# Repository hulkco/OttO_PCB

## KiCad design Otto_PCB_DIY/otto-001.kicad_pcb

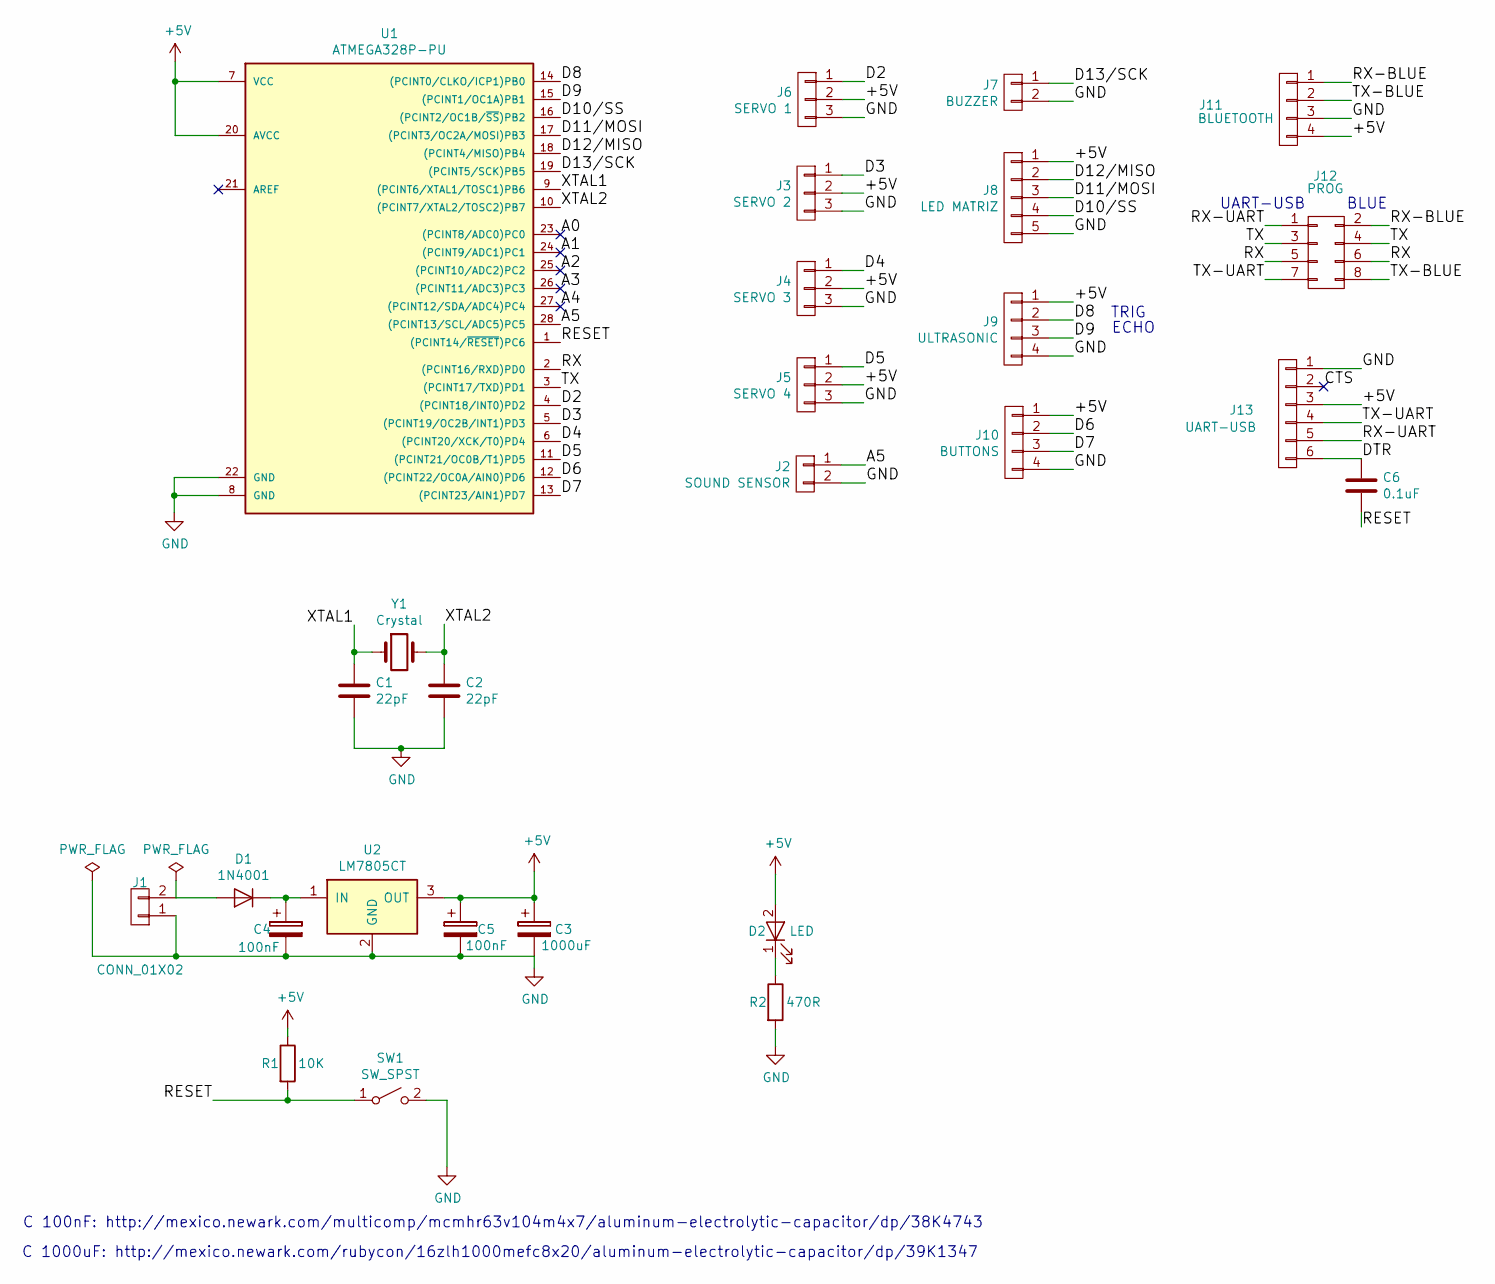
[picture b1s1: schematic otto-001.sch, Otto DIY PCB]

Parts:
C1, C2: 22pF; C_Disc_D5.0mm_W2.5mm_P2.50mm
C3: 1000uF; CP_Radial_D8.0mm_P3.50mm
C4, C5: 100nF; CP_Radial_D4.0mm_P1.50mm
C6: 0.1uF; C_Disc_D5.0mm_W2.5mm_P2.50mm
D1: 1N4001; DIODE-DO-41
D2: LED; LED_D3.0mm
J1: CONN_01X02; Pin_Header_Straight_1x02_Pitch2.54mm
J2: SOUND SENSOR; Pin_Header_Straight_1x02_Pitch2.54mm
J3: SERVO 2; Pin_Header_Straight_1x03_Pitch2.54mm
J4: SERVO 3; Pin_Header_Straight_1x03_Pitch2.54mm
J5: SERVO 4; Pin_Header_Straight_1x03_Pitch2.54mm
J6: SERVO 1; Pin_Header_Straight_1x03_Pitch2.54mm
J7: BUZZER; Pin_Header_Straight_1x02_Pitch2.54mm
J8: LED MATRIZ; Pin_Header_Straight_1x05_Pitch2.54mm
J9: ULTRASONIC; Pin_Header_Straight_1x04_Pitch2.54mm
J10: BUTTONS; Pin_Header_Straight_1x04_Pitch2.54mm
J11: BLUETOOTH; Pin_Header_Straight_1x04_Pitch2.54mm
J12: PROG; Socket_Strip_Straight_2x04_Pitch2.54mm
J13: UART-USB; Pin_Header_Straight_1x06_Pitch2.54mm
R1: 10K; R_Axial_DIN0207_L6.3mm_D2.5mm_P10.16mm_Horizontal
R2: 470R; R_Axial_DIN0207_L6.3mm_D2.5mm_P10.16mm_Horizontal
SW1: SW_SPST; SW_PUSH_6mm_h4.3mm
U1: ATMEGA328P-PU; DIP-28_W7.62mm
U2: LM7805CT; TO-220_Horizontal
Y1: Crystal; Crystal_HC49-U_Vertical

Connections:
+5V: C3.1, C5.1, D2.2 (A), J3.2, J4.2, J5.2, J6.2, J8.1, J9.1, J10.1, J11.4, J13.3, R1.1, U1.7 (VCC), U1.20 (AVCC), U2.3 (OUT)
/A0: U1.23 ((PCINT8/ADC0)PC0)
/A1: U1.24 ((PCINT9/ADC1)PC1)
/A2: U1.25 ((PCINT10/ADC2)PC2)
/A3: U1.26 ((PCINT11/ADC3)PC3)
/A4: U1.27 ((PCINT12/SDA/ADC4)PC4)
/A5: J2.1, U1.28 ((PCINT13/SCL/ADC5)PC5)
/CTS: J13.2
/D2: J6.1, U1.4 ((PCINT18/INT0)PD2)
/D3: J3.1, U1.5 ((PCINT19/OC2B/INT1)PD3)
/D4: J4.1, U1.6 ((PCINT20/XCK/T0)PD4)
/D5: J5.1, U1.11 ((PCINT21/OC0B/T1)PD5)
/D6: J10.2, U1.12 ((PCINT22/OC0A/AIN0)PD6)
/D7: J10.3, U1.13 ((PCINT23/AIN1)PD7)
/D8: J9.2, U1.14 ((PCINT0/CLKO/ICP1)PB0)
/D9: J9.3, U1.15 ((PCINT1/OC1A)PB1)
/D10/SS: J8.4, U1.16 ((PCINT2/OC1B/~SS~)PB2)
/D11/MOSI: J8.3, U1.17 ((PCINT3/OC2A/MOSI)PB3)
/D12/MISO: J8.2, U1.18 ((PCINT4/MISO)PB4)
/D13/SCK: J7.1, U1.19 ((PCINT5/SCK)PB5)
/DTR: C6.1, J13.6
/RESET: C6.2, R1.2, SW1.1 (A), U1.1 ((PCINT14/~RESET~)PC6)
/RX: J12.5, J12.6, U1.2 ((PCINT16/RXD)PD0)
/RX-BLUE: J11.1, J12.2
/RX-UART: J12.1, J13.5
/TX: J12.3, J12.4, U1.3 ((PCINT17/TXD)PD1)
/TX-BLUE: J11.2, J12.8
/TX-UART: J12.7, J13.4
/XTAL1: C1.1, U1.9 ((PCINT6/XTAL1/TOSC1)PB6), Y1.1
/XTAL2: C2.1, U1.10 ((PCINT7/XTAL2/TOSC2)PB7), Y1.2
GND: C1.2, C2.2, C3.2, C4.2, C5.2, J1.1, J2.2, J3.3, J4.3, J5.3, J6.3, J7.2, J8.5, J9.4, J10.4, J11.3, J13.1, R2.2, SW1.2 (B), U1.8 (GND), U1.22 (GND), U2.2 (GND)
unnamed: C4.1, D1.1 (K), U2.1 (IN)
unnamed: D1.2 (A), J1.2
unnamed: D2.1 (K), R2.1

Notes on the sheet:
TRIG
ECHO
C 100nF: http://mexico.newark.com/multicomp/mcmhr63v104m4x7/aluminum-electrolytic-capacitor/dp/38K4743
C 1000uF: http://mexico.newark.com/rubycon/16zlh1000mefc8x20/aluminum-electrolytic-capacitor/dp/39K1347
UART-USB
BLUE

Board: 2 copper layers, 33 parts (0 on the bottom side), 28 nets, no tracks yet.

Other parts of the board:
GBSilk***: LOGO; greynaga6-2
GS***: v; greynaga6-2-cooper
HOLE1, HOLE2, HOLE3, HOLE4: MountingHole_2.2mm_M2_Pad_Via

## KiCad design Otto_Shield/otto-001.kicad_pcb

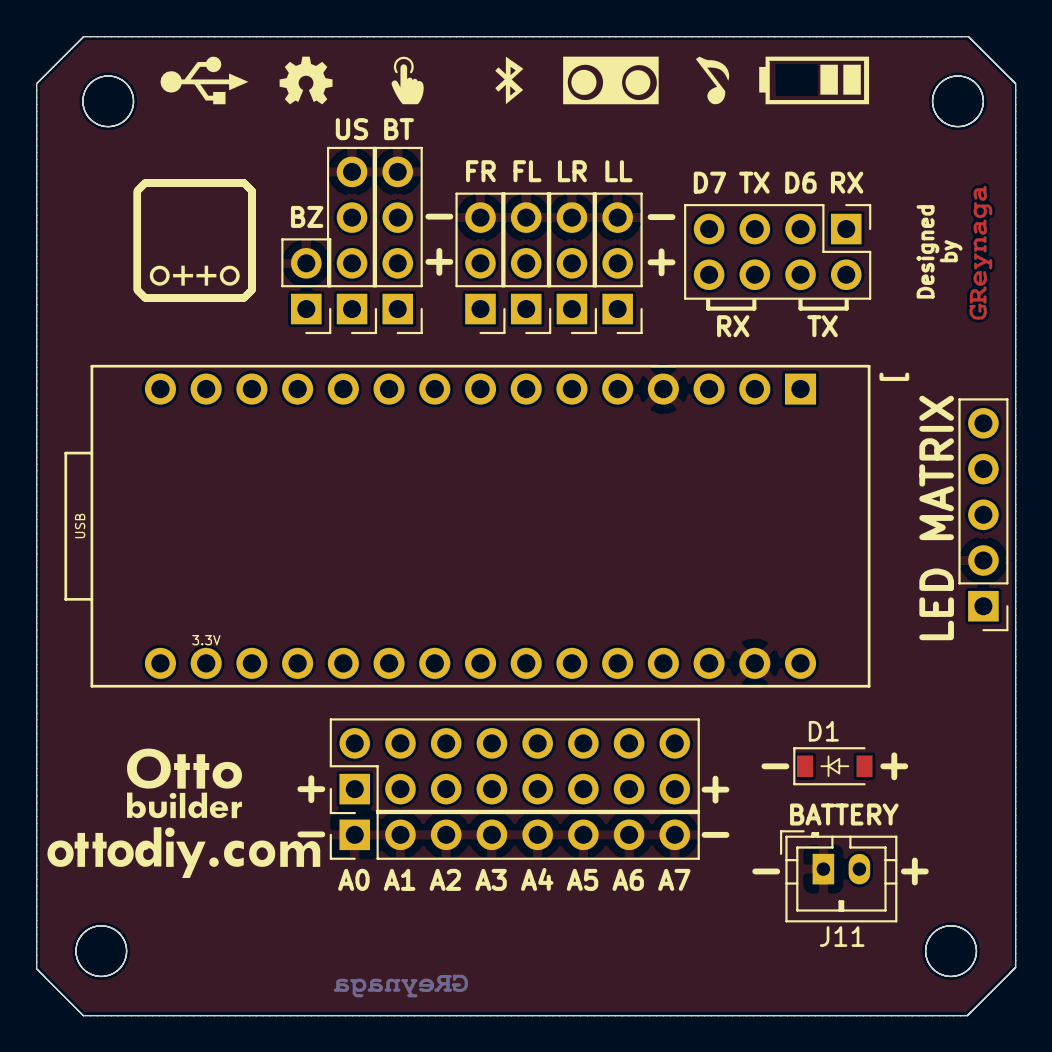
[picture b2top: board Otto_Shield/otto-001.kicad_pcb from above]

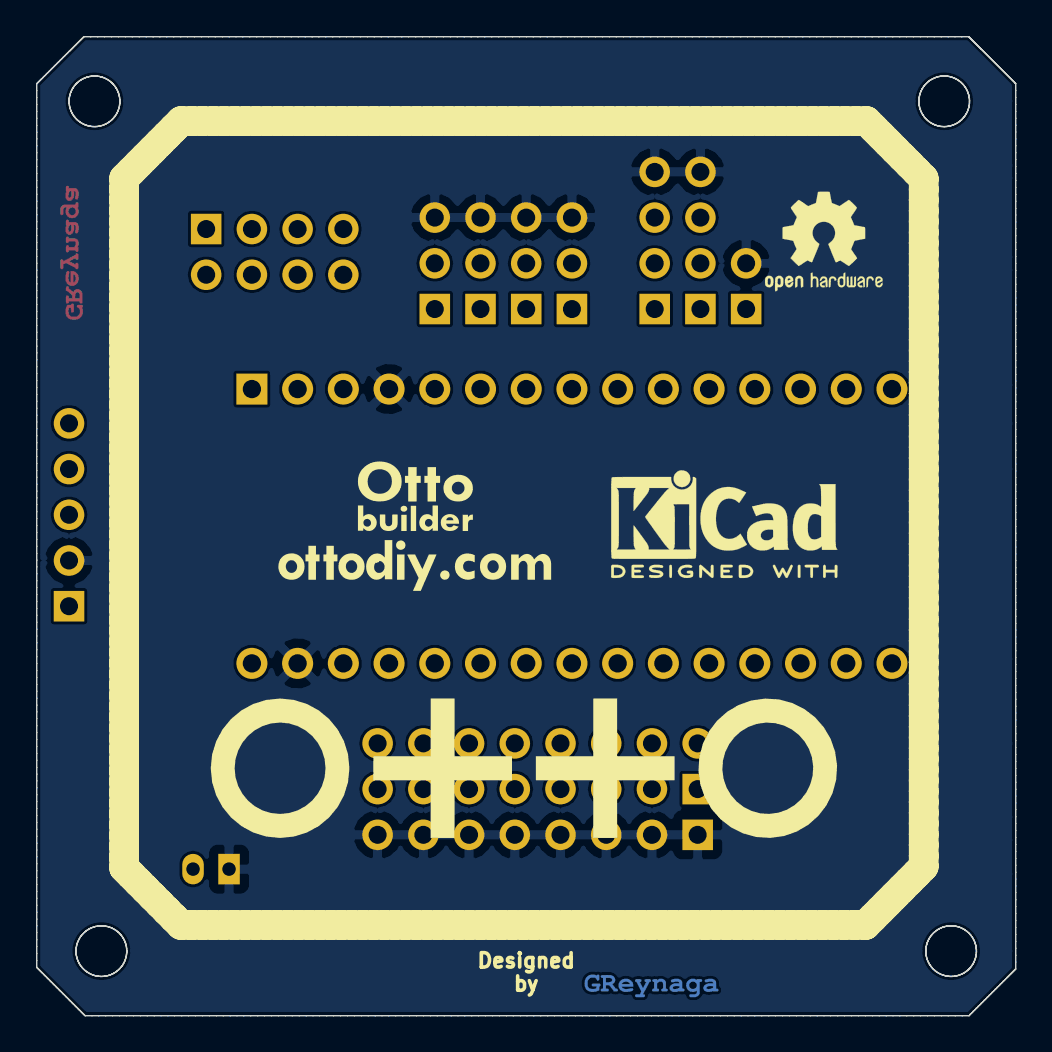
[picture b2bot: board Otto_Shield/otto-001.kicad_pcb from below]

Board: 2 copper layers, 54.4 x 54.4 mm, 25 parts (4 on the bottom side), 29 nets, no tracks yet.

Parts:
BatMask: BatMask***; OttO_Batt_Bar_Mask
D1: MBRA140; D_SOD-123
EdgeCutSilkS: EdgeCutSilkS***; OttO_EdgeCuts
GSLogoMask: GSLogoMask***; greynaga6-2
GSLogoMask1: GSLogoMask1***; greynaga6-2
GSlogoCu: GSlogoCu***; greynaga6-2-cooper
GSlogoCu1: GSlogoCu1***; greynaga6-2-cooper
IconsSilkS: IconsSilkS***; OttO_Icons_SilkS
J1: LegRight; Pin_Header_Straight_1x03_Pitch2.54mm
J2: LegLeft; Pin_Header_Straight_1x03_Pitch2.54mm
J3: BLUETOOTH; Pin_Header_Straight_1x04_Pitch2.54mm
J4: FootRight; Pin_Header_Straight_1x03_Pitch2.54mm
J5: FootLeft; Pin_Header_Straight_1x03_Pitch2.54mm
J6: BLUETOOTH RX-TX; Pin_Header_Straight_2x04_Pitch2.54mm
J7: ULTRASONIC; Pin_Header_Straight_1x04_Pitch2.54mm
J8: LED MATRIX; Pin_Header_Straight_1x05_Pitch2.54mm
J9: BUZZER; Pin_Header_Straight_1x02_Pitch2.54mm
J10: ANALOG; Pin_Header_Straight_2x08_Pitch2.54mm
J11: BATTERY; JST_PH_B2B-PH-K_02x2.00mm_Straight
J12: ANALOG-GND; Pin_Header_Straight_1x08_Pitch2.54mm
LogoBigSilkS: LogoBigSilkS***; OttO_Logo_Big_SilkS
LogoSilkS: LogoSilkS***; OttO_Logo_SilkS
URLSilkS: URLSilkS***; OttO_URL_SilkS
XA1: Arduino_Nano_Socket; Arduino_Nano_Socket_02
svg2mod: G***; OttO_URL_SilkS

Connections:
/+5V: J1.2, J2.2, J3.3, J4.2, J5.2, J7.1, J8.1, J10.1, J10.3, J10.5, J10.7, J10.9, J10.11, J10.13, J10.15, XA1.5V
/A0: J10.2, XA1.A0
/A1: J10.4, XA1.A1
/A2: J10.6, XA1.A2
/A3: J10.8, XA1.A3
/A4: J10.10, XA1.A4
/A5: J10.12, XA1.A5
/A6: J10.14, XA1.A6
/A7: J10.16, XA1.A7
/D2: J2.1, XA1.D2
/D3: J1.1, XA1.D3
/D4: J5.1, XA1.D4
/D5: J4.1, XA1.D5
/D6: J6.3, XA1.D6
/D7: J6.7, XA1.D7
/D8: J7.2, XA1.D8
/D9: J7.3, XA1.D9
/D10/SS: J8.3, XA1.D10
/D11/MOSI: J8.4, XA1.D11
/D12/MISO: J8.5, XA1.D12
/D13/SCK: J9.1, XA1.D13
/RESET: XA1.RST1, XA1.RST2
/RX: J3.1, J6.1, XA1.D0
/RX-B: J6.6, J6.8
/TX: J3.2, J6.5, XA1.D1
/TX-B: J6.2, J6.4
/VIN: D1.1, XA1.VIN
GND: J1.3, J2.3, J3.4, J4.3, J5.3, J7.4, J8.2, J9.2, J11.1, J12.1, J12.2, J12.3, J12.4, J12.5, J12.6, J12.7, J12.8, XA1.GND1, XA1.GND2
unnamed: D1.2, J11.2

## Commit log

2019-02-07 Firts upload
2019-02-07 Update names
